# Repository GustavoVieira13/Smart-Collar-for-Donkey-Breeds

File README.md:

# Smart-Collar-for-Donkey-Breeds
Smart Collar for Donkey Breeds embedding sensors that track humidity, air temperature, air pressure, orientation and acceleration. Communicating through LoRaWAN.

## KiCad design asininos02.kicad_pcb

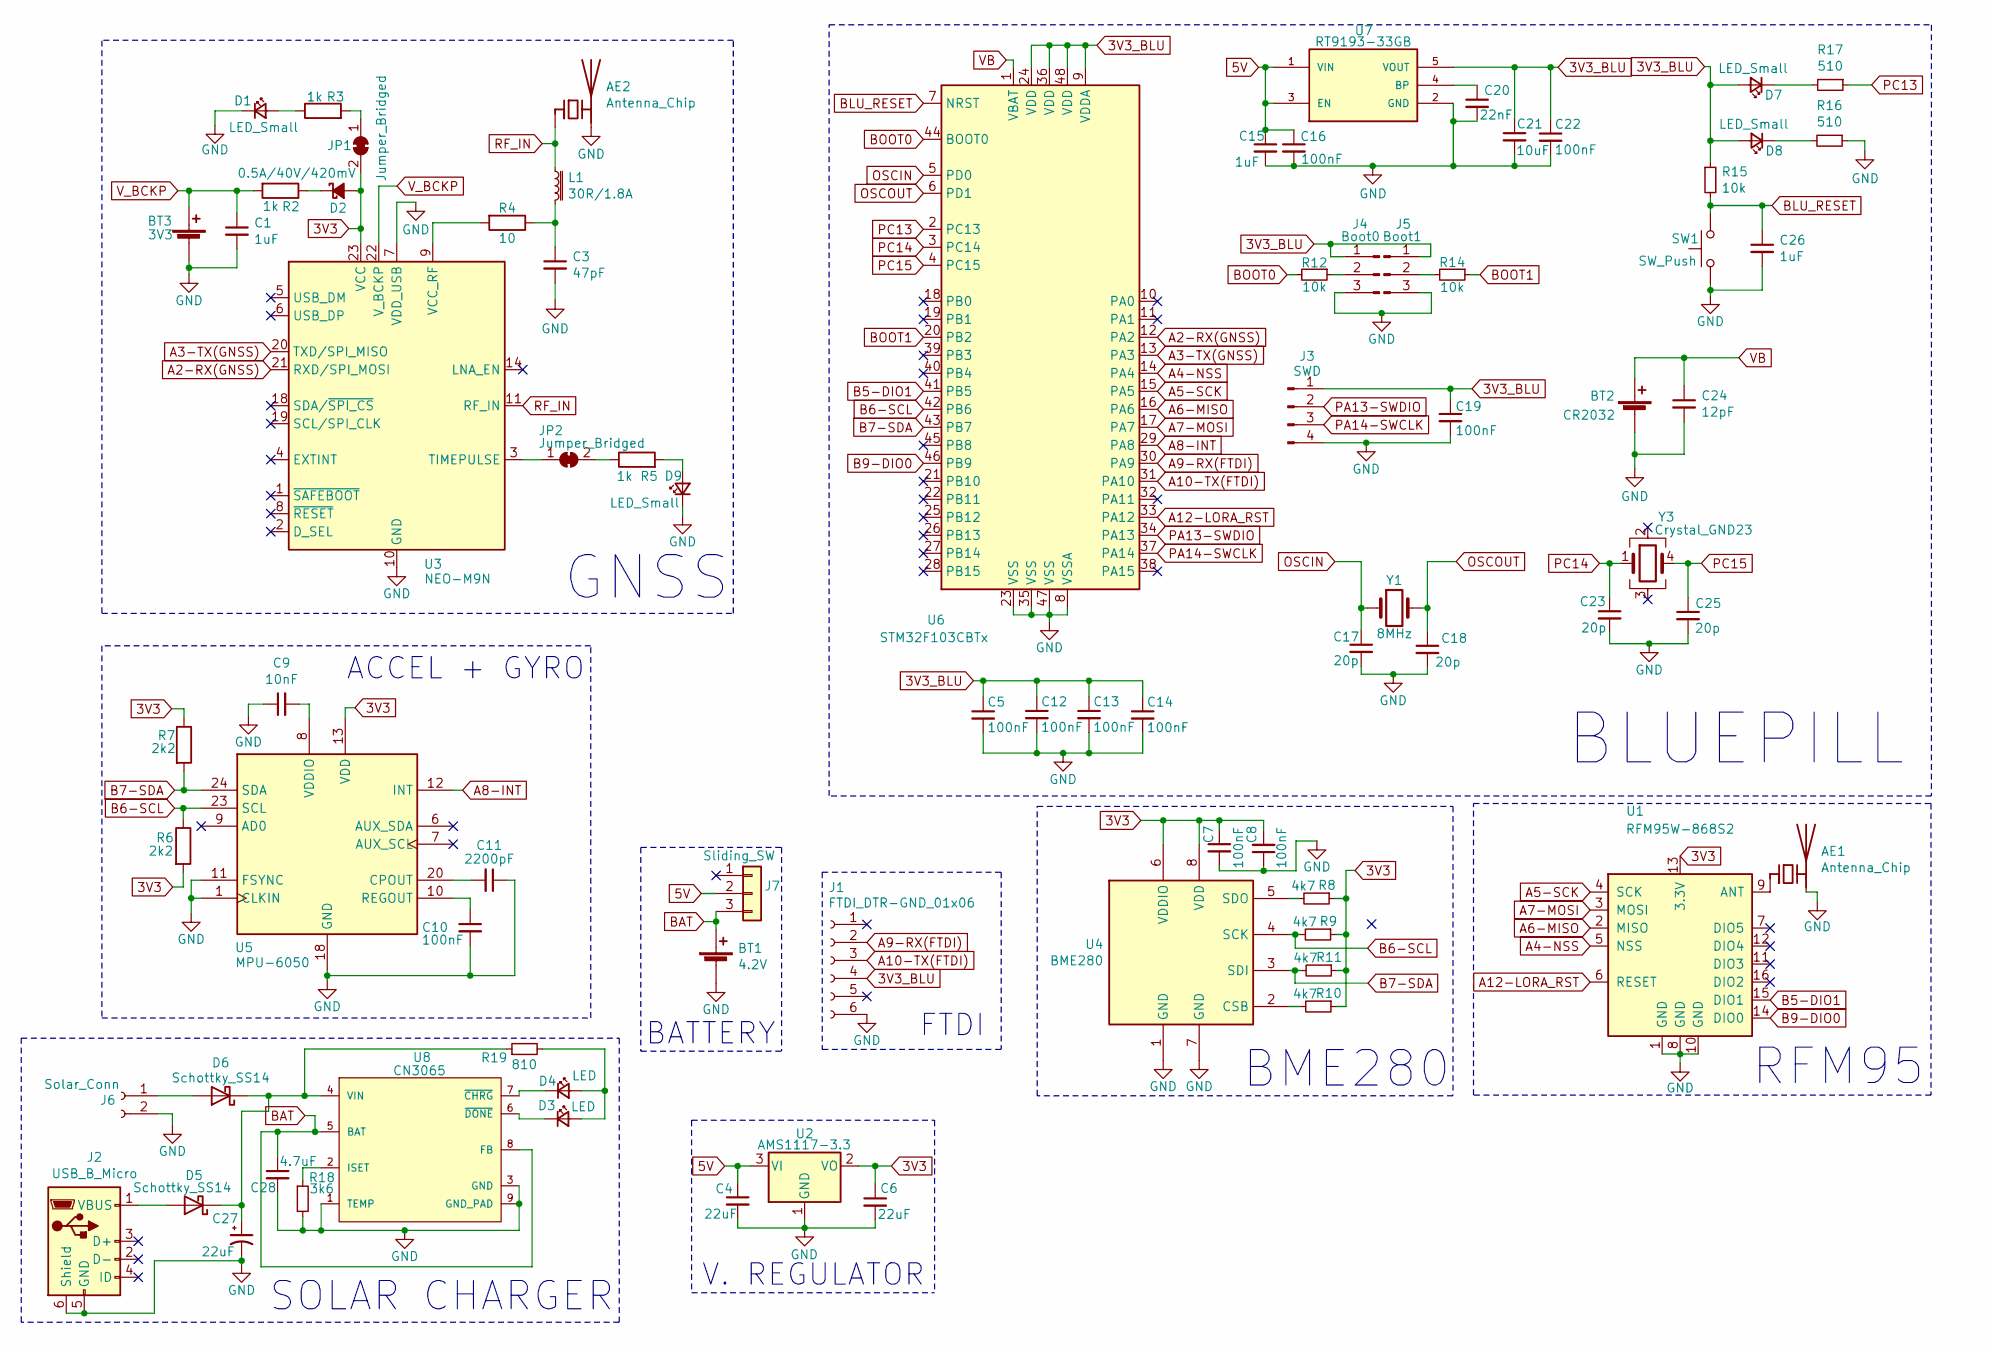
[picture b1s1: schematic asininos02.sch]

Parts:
AE1, AE2: Antenna_Chip; U.FL_Hirose_U.FL-R-SMT-1_Vertical
BT1: 4.2V; BatteryHolder_MPD_BH-18650-PC2
BT2: CR2032; BatteryHolder_Keystone_1058_1x2032
BT3: 3V3; SEIKO_ML414H_IV01E
C1, C15, C26: 1uF; C_0805_2012Metric_Pad1.18x1.45mm_HandSolder
C3: 47pF; C_0805_2012Metric_Pad1.18x1.45mm_HandSolder
C4, C6: 22uF; C_0805_2012Metric_Pad1.18x1.45mm_HandSolder
C5, C7, C8, C10, C12, C13, C14, C16, C19, C22: 100nF; C_0805_2012Metric_Pad1.18x1.45mm_HandSolder
C9: 10nF; C_0805_2012Metric_Pad1.18x1.45mm_HandSolder
C11: 2200pF; C_0805_2012Metric_Pad1.18x1.45mm_HandSolder
C17, C18, C23, C25: 20p; C_0805_2012Metric_Pad1.18x1.45mm_HandSolder
C20: 22nF; C_0805_2012Metric_Pad1.18x1.45mm_HandSolder
C21: 10uF; C_0805_2012Metric_Pad1.18x1.45mm_HandSolder
C24: 12pF; C_0805_2012Metric_Pad1.18x1.45mm_HandSolder
C27: 22uF; CP_EIA-3528-21_Kemet-B
C28: 4.7uF; C_0805_2012Metric_Pad1.18x1.45mm_HandSolder
D1, D7, D8, D9: LED_Small; LED_0805_2012Metric_Pad1.15x1.40mm_HandSolder
D2: 0.5A/40V/420mV; D_SOD-123
D3, D4: LED; LED_0805_2012Metric_Pad1.15x1.40mm_HandSolder
D5, D6: Schottky_SS14; D_SMA
J1: FTDI_DTR-GND_01x06; PinSocket_1x06_P2.54mm_Vertical
J2: USB_B_Micro; USB_Micro-B_Molex_47346-0001
J3: SWD; PinHeader_1x04_P2.54mm_Vertical
J4: Boot0; PinHeader_1x03_P2.54mm_Vertical
J5: Boot1; PinHeader_1x03_P2.54mm_Vertical
J6: Solar_Conn; JST_XH_B2B-XH-A_1x02_P2.50mm_Vertical
J7: Sliding_SW; PinSocket_1x03_P2.54mm_Vertical
JP1, JP2: Jumper_Bridged; SolderJumper-2_P1.3mm_Bridged_RoundedPad1.0x1.5mm
L1: 30R/1.8A; L_0603_1608Metric_Pad1.05x0.95mm_HandSolder
R2, R3, R5: 1k; R_0805_2012Metric_Pad1.20x1.40mm_HandSolder
R4: 10; R_0805_2012Metric_Pad1.20x1.40mm_HandSolder
R6, R7: 2k2; R_0805_2012Metric_Pad1.20x1.40mm_HandSolder
R8, R9, R10, R11: 4k7; R_0805_2012Metric_Pad1.20x1.40mm_HandSolder
R12, R14, R15: 10k; R_0805_2012Metric_Pad1.20x1.40mm_HandSolder
R16, R17: 510; R_0805_2012Metric_Pad1.20x1.40mm_HandSolder
R18: 3k6; R_0805_2012Metric_Pad1.20x1.40mm_HandSolder
R19: 810; R_0805_2012Metric_Pad1.20x1.40mm_HandSolder
SW1: SW_Push; SW_SPST_CK_RS282G05A3
U1: RFM95W-868S2; HOPERF_RFM9XW_SMD
U2: AMS1117-3.3; SOT-223-3_TabPin2
U3: NEO-M9N; ublox_NEO
U4: BME280; Bosch_LGA-8_2.5x2.5mm_P0.65mm_ClockwisePinNumbering
U5: MPU-6050; InvenSense_QFN-24_4x4mm_P0.5mm_NoMask
U6: STM32F103CBTx; LQFP-48_7x7mm_P0.5mm
U7: RT9193-33GB; SOT-23-5
U8: CN3065; DFN-8-1EP_3x3mm_P0.5mm_EP1.66x2.38mm; voltage 6V
Y1: 8MHz; Crystal_HC49-4H_Vertical
Y3: Crystal_GND23; Crystal_SMD_SeikoEpson_MC306-4Pin_8.0x3.2mm

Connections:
3V3: C6.1, C7.1, C8.2, D2.2 (A), JP1.2 (B), R6.2, R7.1, R8.1, R9.1, R10.1, R11.1, U1.13 (3.3V), U2.2 (VO), U3.23 (VCC), U4.6 (VDDIO), U4.8 (VDD), U5.13 (VDD)
3V3_BLU: C5.1, C12.1, C13.1, C14.1, C19.1, C21.1, C22.1, D7.2 (A), D8.2 (A), J1.4, J3.1, J4.1, J5.1, R15.1, U6.9 (VDDA), U6.24 (VDD), U6.36 (VDD), U6.48 (VDD), U7.5 (VOUT)
5V: C4.1, C15.1, C16.1, J7.2, U2.3 (VI), U7.1 (VIN), U7.3 (EN)
A2-RX(GNSS): U3.21 (RXD/SPI_MOSI), U6.12 (PA2)
A3-TX(GNSS): U3.20 (TXD/SPI_MISO), U6.13 (PA3)
A4-NSS: U1.5 (NSS), U6.14 (PA4)
A5-SCK: U1.4 (SCK), U6.15 (PA5)
A6-MISO: U1.2 (MISO), U6.16 (PA6)
A7-MOSI: U1.3 (MOSI), U6.17 (PA7)
A8-INT: U5.12 (INT), U6.29 (PA8)
A9-RX(FTDI): J1.2, U6.30 (PA9)
A10-TX(FTDI): J1.3, U6.31 (PA10)
A12-LORA_RST: U1.6 (RESET), U6.33 (PA12)
B5-DIO1: U1.15 (DIO1), U6.41 (PB5)
B6-SCL: R6.1, R9.2, U4.4 (SCK), U5.23 (SCL), U6.42 (PB6)
B7-SDA: R7.2, R11.2, U4.3 (SDI), U5.24 (SDA), U6.43 (PB7)
B9-DIO0: U1.14 (DIO0), U6.46 (PB9)
BAT: BT1.1 (+), C28.1, J7.3, U8.5 (BAT), U8.8 (FB)
BLU_RESET: C26.1, R15.2, SW1.2, U6.7 (NRST)
BOOT0: R12.2, U6.44 (BOOT0)
BOOT1: R14.1, U6.20 (PB2)
GND: AE1.2 (PCB_Trace), AE2.2 (PCB_Trace), BT1.2 (-), BT2.2 (-), BT3.2 (-), C1.2, C3.2, C4.2, C5.2, C6.2, C7.2, C8.1, C9.1, C10.2, C11.1, C12.2, C13.2, C14.2, C15.2, C16.2, C17.2, C18.2, C19.2, C20.2, C21.2, C22.2, C23.2, C24.2, C25.2, C26.2, C27.2, C28.2, D1.1 (K), D9.1 (K), J1.6, J2.5 (GND), J2.6 (Shield), J3.4, J4.3, J5.3, J6.2, R16.1, R18.2, SW1.1, U1.1 (GND), U1.8 (GND), U1.10 (GND), U2.1 (GND), U3.7 (VDD_USB), U3.10 (GND), U3.12 (GND), U3.13 (GND), U3.24 (GND), U4.1 (GND), U4.7 (GND), U5.1 (CLKIN), U5.11 (FSYNC), U5.18 (GND), U6.8 (VSSA), U6.23 (VSS), U6.35 (VSS), U6.47 (VSS), U7.2 (GND), U8.1 (TEMP), U8.3 (GND), U8.9 (GND_PAD)
unnamed: AE1.1 (FEED), U1.9 (ANT)
unnamed: C3.1, L1.2, R4.1
unnamed: C9.2, U5.8 (VDDIO)
unnamed: C10.1, U5.10 (REGOUT)
unnamed: C11.2, U5.20 (CPOUT)
unnamed: C20.1, U7.4 (BP)
unnamed: C27.1, D5.1 (K), D6.1 (K), R19.1, U8.4 (VIN)
unnamed: D1.2 (A), R3.1
unnamed: D2.1 (K), R2.1
unnamed: D3.1 (K), U8.6 (~DONE~)
unnamed: D3.2 (A), D4.2 (A), R19.2
unnamed: D4.1 (K), U8.7 (~CHRG~)
unnamed: D5.2 (A), J2.1 (VBUS)
unnamed: D6.2 (A), J6.1
unnamed: D7.1 (K), R17.2
unnamed: D8.1 (K), R16.2
unnamed: D9.2 (A), R5.2
unnamed: J4.2, R12.1
unnamed: J5.2, R14.2
unnamed: JP1.1 (A), R3.2
unnamed: JP2.1 (A), U3.3 (TIMEPULSE)
unnamed: JP2.2 (B), R5.1
unnamed: R4.2, U3.9 (VCC_RF)
unnamed: R8.2, U4.5 (SDO)
unnamed: R10.2, U4.2 (CSB)
unnamed: R18.1, U8.2 (ISET)
OSCIN: C17.1, U6.5 (PD0), Y1.1
OSCOUT: C18.1, U6.6 (PD1), Y1.2
PA13-SWDIO: J3.2, U6.34 (PA13)
PA14-SWCLK: J3.3, U6.37 (PA14)
PC13: R17.1, U6.2 (PC13)
PC14: C23.1, U6.3 (PC14), Y3.1
PC15: C25.1, U6.4 (PC15), Y3.4
RF_IN: AE2.1 (FEED), L1.1, U3.11 (RF_IN)
VB: BT2.1 (+), C24.1, U6.1 (VBAT)
V_BCKP: BT3.1 (+), C1.1, R2.2, U3.22 (V_BCKP)

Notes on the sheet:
BLUEPILL
RFM95
BME280
GNSS
V. REGULATOR
FTDI
ACCEL + GYRO
BATTERY
SOLAR CHARGER

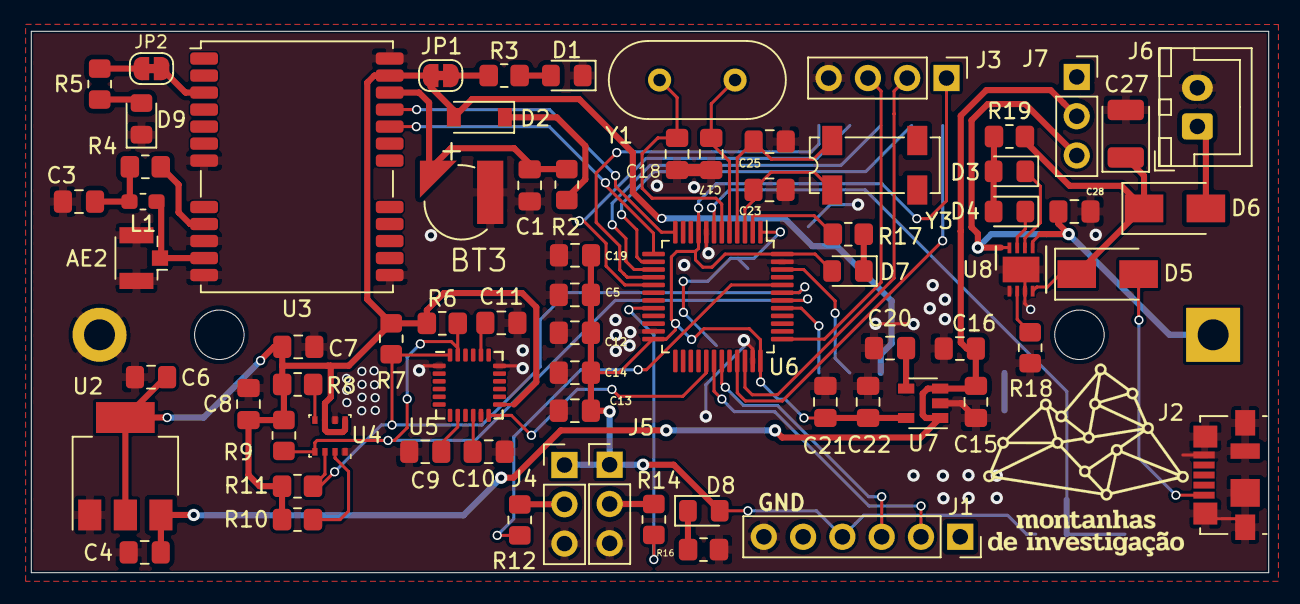
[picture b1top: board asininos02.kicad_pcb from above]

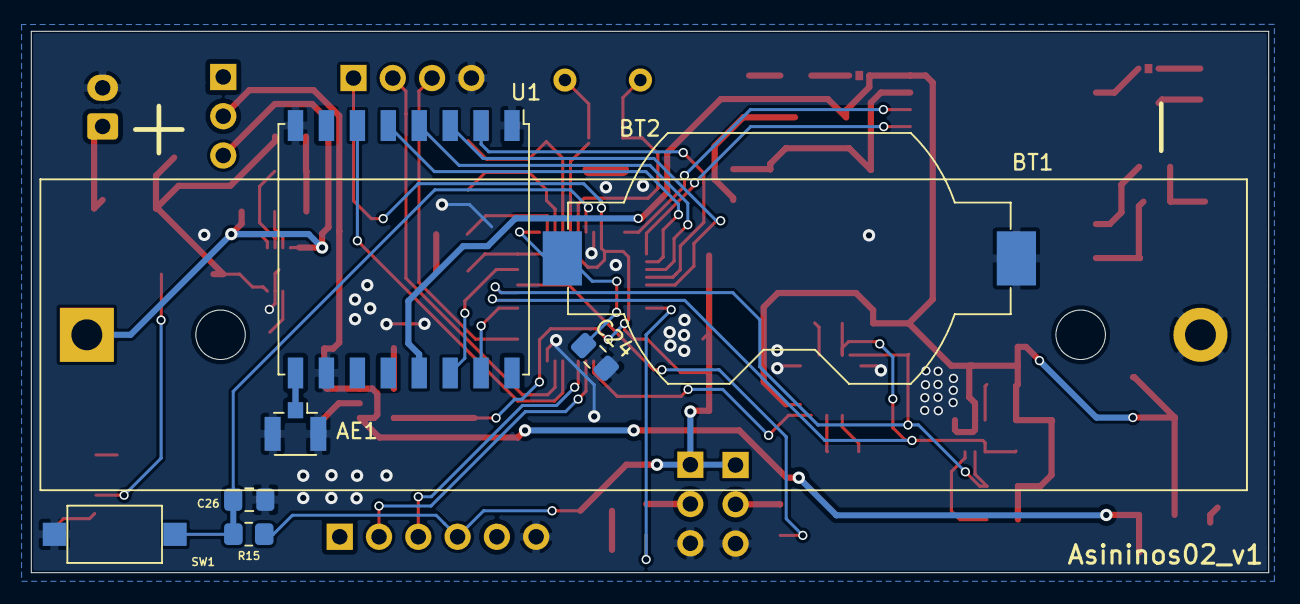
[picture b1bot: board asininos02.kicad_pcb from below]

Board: 2 copper layers, 80.0 x 35.0 mm, 79 parts (8 on the bottom side), 58 nets.
